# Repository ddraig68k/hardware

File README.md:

# CAD files for Y Ddraig

This repository contains the Schematics and any other relevant files for a [Motorola 68000 computer](https://ddraig68k.com) in KiCAD format. The files for the main computer boards as well as any of the expansion boards are present in the repository.

The libraries used in the project are contained in the ddraig-libs folder inside the repo, to use them in KiCAD, go to Configure Paths and add a custom path DDRAIGLIB which points to the ddraig-libs folder.

## Y Ddraig

Welsh for *The Dragon*, Y Ddraig is my [Motorola 68000](https://en.wikipedia.org/wiki/Motorola_68000) computer. 

| **Specifications** |
|-|
|68000 CPU running at 10Mhz.|
|512K EEPROM |
|1M of Static RAM|
|8M Dynamic RAM|
|2 Serial ports|
|Parallel port|
|PS/2 keyboard and mouse|
|IDE interface|
|Real-time clock|
|4 Expansion slots|

<br />

# Design Files
[Y Ddraig 68000 PCB](yddraig)

**Expansion Cards**

* [Dual SID Audio card](expansion/AudioSID) - two MOS 6581/8580 SID chips for Commodore 64 style audio

* [YM2151 Audio card](expansion/AudioYM2151) - Yamaha FM synthesis chip as used in many arcade games

* [RTL8019 Ethernet card](expansion/Eth8019) - 10BASE-T Ethernet using the Realtek RTL8019AS

* [TMS9918 Graphics card](expansion/GfxTMS9918) - the video chip used in the Sega SG-1000, ColecoVision and MSX1

* [V9958 Graphics card](expansion/GfxV9958) - Yamaha's successor to the TMS9918, as used in the MSX2+

* [V9990 Graphics card](expansion/GfxV9990) - Yamaha's follow up to the V9958 with higher resolutions

* [VGA Graphics card](expansion/GfxVGA) - FPGA based VGA video generation

* [Sega Megadrive joypad card](expansion/JoypadController) - reads standard 3 or 6-button Sega Megadrive/Genesis controllers

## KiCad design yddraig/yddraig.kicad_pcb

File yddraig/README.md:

## Y Ddraig hardware

### CPU, RAM and ROM

The CPU used by Y Ddraig is the [Motorola 68000](https://en.wikipedia.org/wiki/Motorola_68000) running at 10 MHz. The 68000 has a 16-bit data bus and 24-bit address bus internally runs as a full 32-bit machine. The 68000 has 8 general purpose data registers *D0-D7* and 8 address registers *A0-A7*. The address register A7 is also used as a special purpose register holding the *stack pointer*.

There is 512K of EEPROM available supplied by two 256K x 8-bit SST39SF020 devices for the ODD and EVEN addresses.

RAM is provided by two 512K x 8-bit AS6C4008 Static RAM devices giving a total of 1024K of available memory. There is also the option of adding an additional Dynamic RAM to expand the memory up to a total of 9MB.

### Memory Mapping

As the 68000 is a memory mapped device the address decoding is handled by a Xilinx XC95C108 CPLD. In addition to the address decoding the CPLD is also used as the DRAM controller.

The memory map is as follows:

| Device | Start Address | End Address |
|-|-|-|
| Static Ram | 0x000000 | 0x0FFFFF |
| Dynamic RAM | 0x100000 | 0x900000 |
| Slot1 Data | 0xA00000 | 0xAFFFFF |
| Slot2 Data | 0xB00000 | 0xBFFFFF |
| Slot3 Data | 0xC00000 | 0xCFFFFF |
| Slot4 Data | 0xD00000 | 0xDFFFFF |
| DUART | 0xF7F000 | 0xF7F0FF |
| PIT | 0xF7F100 | 0xF7F1FF |
| KBD | 0xF7F200 | 0xF7F2FF |
| IDE | 0xF7F300 | 0xF7F3FF |
| RTC | 0xF7F400 | 0xF7F4FF |
| Slot1 | 0xF7F500 | 0xF7F5FF |
| Slot2 | 0xF7F600 | 0xF7F6FF |
| Slot3 | 0xF7F700 | 0xF7F7FF |
| Slot4 | 0xF7F800 | 0xF7F8FF |
| ROM | 0xF80000 | 0xFFFFFF |

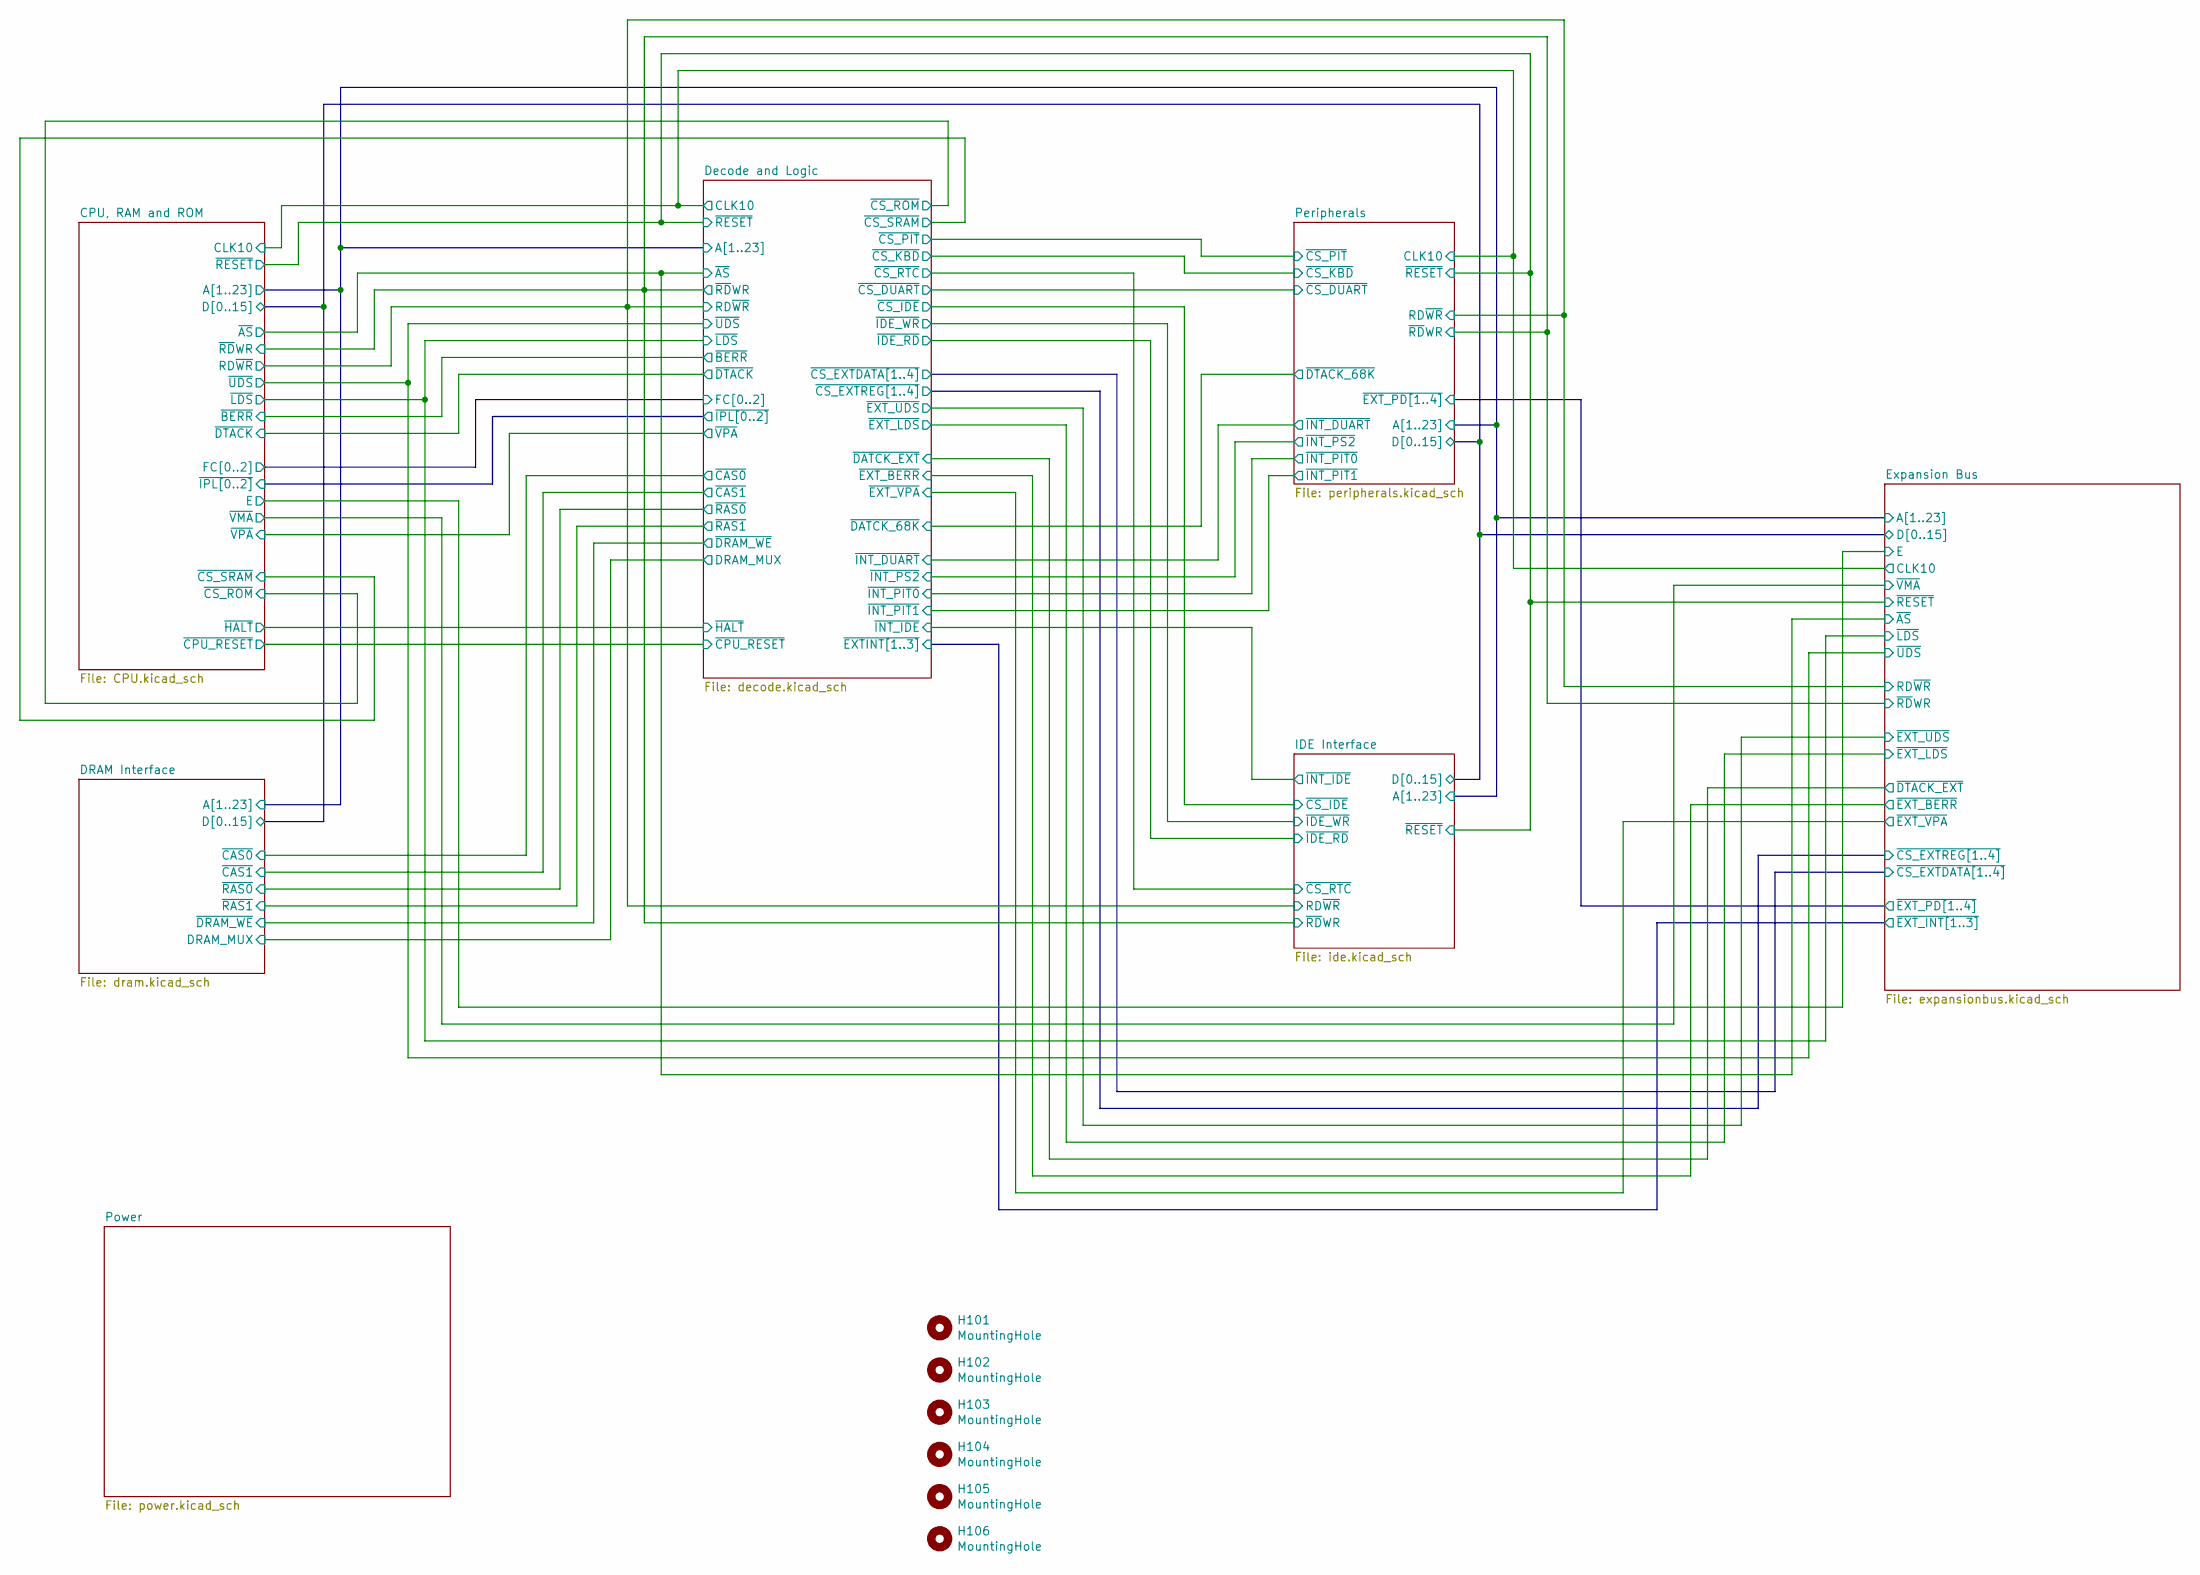
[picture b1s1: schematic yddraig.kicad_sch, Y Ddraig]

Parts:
H101, H102, H103, H104, H105, H106: MountingHole; MountingHole_4.3mm_M4

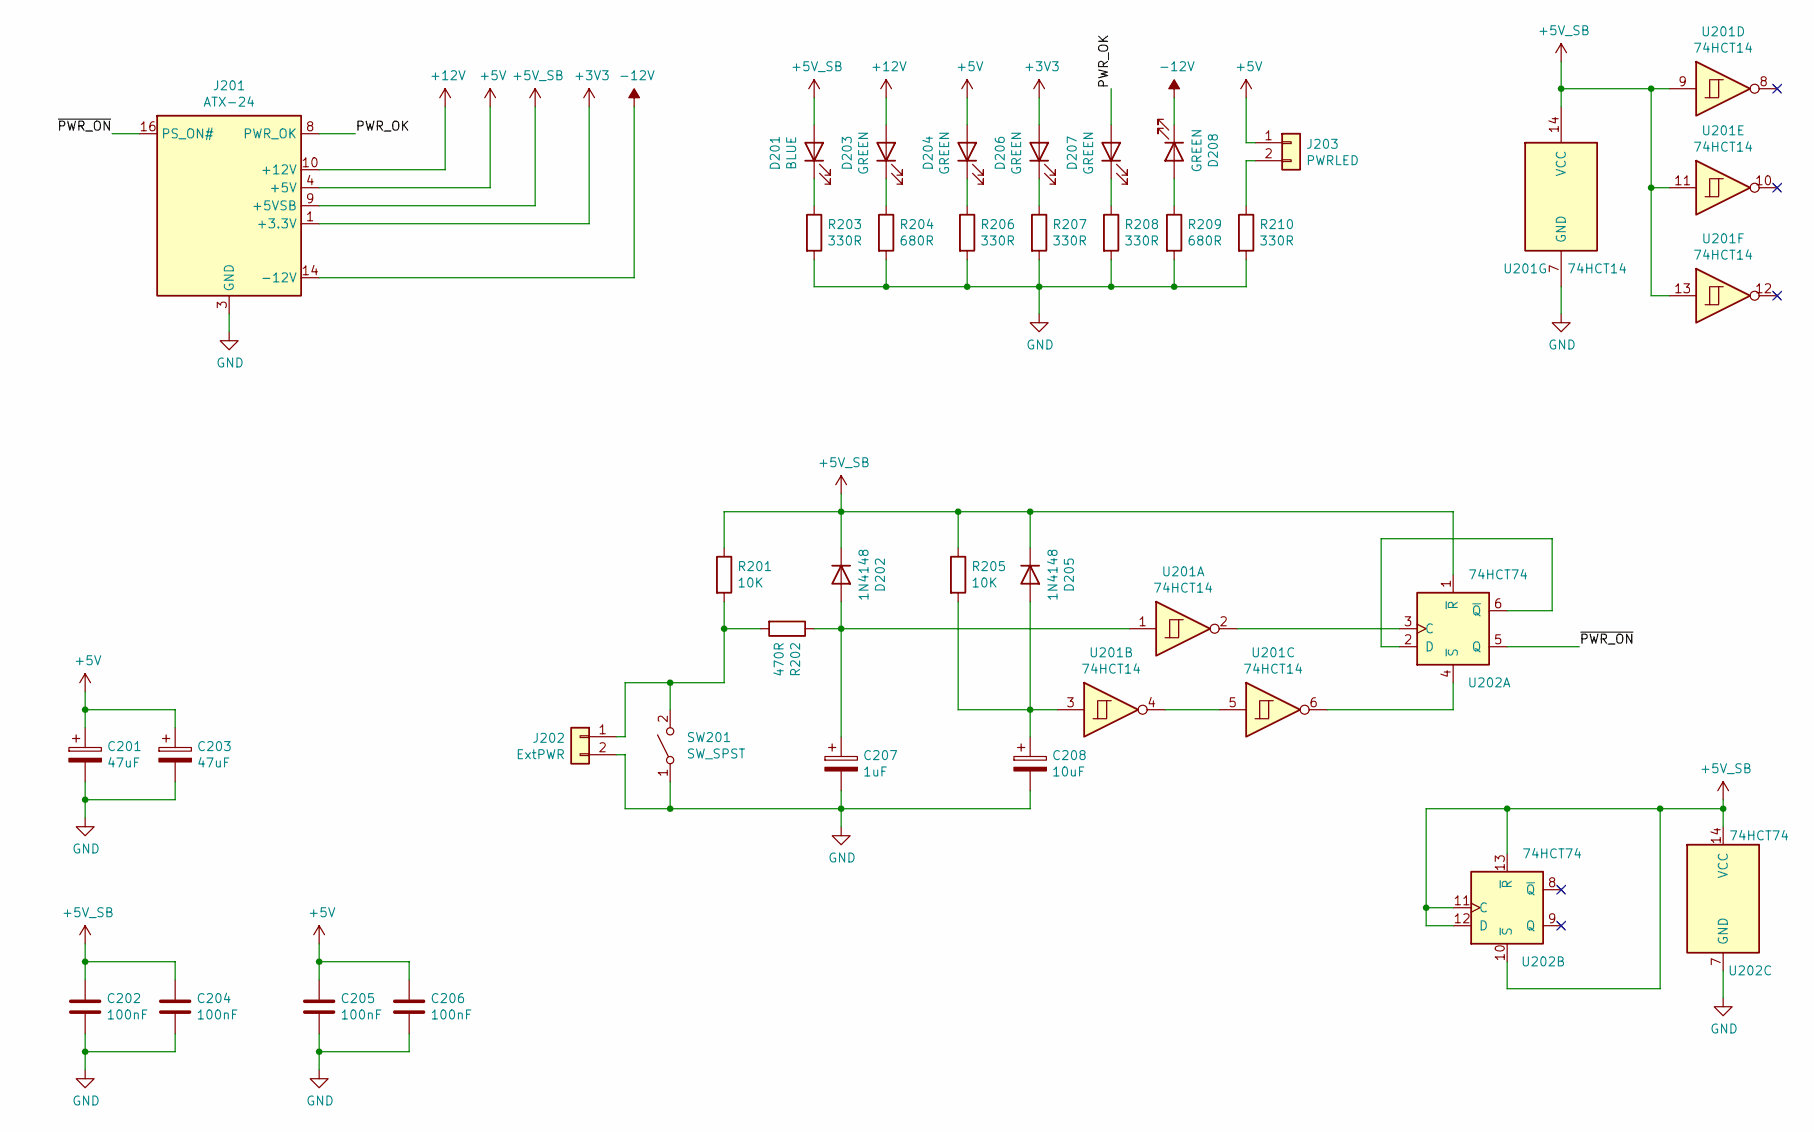
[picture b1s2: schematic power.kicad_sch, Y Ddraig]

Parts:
C201, C203: 47uF; CP_Radial_D5.0mm_P2.50mm
C202, C204, C205, C206: 100nF; C_Disc_D3.8mm_W2.6mm_P2.50mm
C207: 1uF; CP_Radial_D5.0mm_P2.50mm
C208: 10uF; CP_Radial_D5.0mm_P2.50mm
D201: BLUE; LED_D5.0mm
D202, D205: 1N4148; D_DO-35_SOD27_P7.62mm_Horizontal
D203, D204, D206, D207, D208: GREEN; LED_D5.0mm
J201: ATX-24; 1-1775099-3
J202: ExtPWR; PinHeader_1x02_P2.54mm_Vertical
J203: PWRLED; PinHeader_1x02_P2.54mm_Vertical
R201, R205: 10K; R_Axial_DIN0207_L6.3mm_D2.5mm_P10.16mm_Horizontal
R202: 470R; R_Axial_DIN0207_L6.3mm_D2.5mm_P10.16mm_Horizontal
R203, R206, R207, R208, R210: 330R; R_Axial_DIN0207_L6.3mm_D2.5mm_P10.16mm_Horizontal
R204, R209: 680R; R_Axial_DIN0207_L6.3mm_D2.5mm_P10.16mm_Horizontal
SW201: SW_SPST; SW_PUSH_6mm_H4.3mm
U201: 74HCT14; DIP-14_W7.62mm_Socket
U202: 74HCT74; DIP-14_W7.62mm_Socket

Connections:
+3V3: D206.2 (A), J201.1 (+3.3V), J201.2 (+3.3V), J201.12 (+3.3V), J201.13 (+3.3V); also elsewhere on the board
+5V: C201.1, C203.1, C205.1, C206.1, D204.2 (A), J201.4 (+5V), J201.6 (+5V), J201.21 (+5V), J201.22 (+5V), J201.23 (+5V), J203.1; also elsewhere on the board
+5V_SB: C202.1, C204.1, D201.2 (A), D202.1 (K), D205.1 (K), J201.9 (+5VSB), R201.1, R205.1, U201.9, U201.11, U201.13, U201.14 (VCC), U202.1 (~R), U202.10 (~S), U202.11 (C), U202.12 (D), U202.13 (~R), U202.14 (VCC); also elsewhere on the board
+12V: D203.2 (A), J201.10 (+12V), J201.11 (+12V); also elsewhere on the board
-12V: D208.1 (K), J201.14 (-12V); also elsewhere on the board
/Power/PWR_OK: D207.2 (A), J201.8 (PWR_OK)
/Power/~PWR_ON: J201.16 (PS_ON#), U202.5 (Q)
GND: C201.2, C202.2, C203.2, C204.2, C205.2, C206.2, C207.2, C208.2, J201.3 (GND), J201.5 (GND), J201.7 (GND), J201.15 (GND), J201.17 (GND), J201.18 (GND), J201.19 (GND), J201.24 (GND), J202.2, R203.2, R204.2, R206.2, R207.2, R208.2, R209.2, R210.2, SW201.1 (A), U201.7 (GND), U202.7 (GND); also elsewhere on the board
unnamed: D201.1 (K), R203.1
unnamed: C207.1, D202.2 (A), R202.1, U201.1
unnamed: D203.1 (K), R204.1
unnamed: D204.1 (K), R206.1
unnamed: C208.1, D205.2 (A), R205.2, U201.3
unnamed: D206.1 (K), R207.1
unnamed: D207.1 (K), R208.1
unnamed: D208.2 (A), R209.1
unnamed: J202.1, R201.2, R202.2, SW201.2 (B)
unnamed: J203.2, R210.1
unnamed: U201.4, U201.5
unnamed: U201.2, U202.3 (C)
unnamed: U202.2 (D), U202.6 (~Q)
unnamed: U201.6, U202.4 (~S)

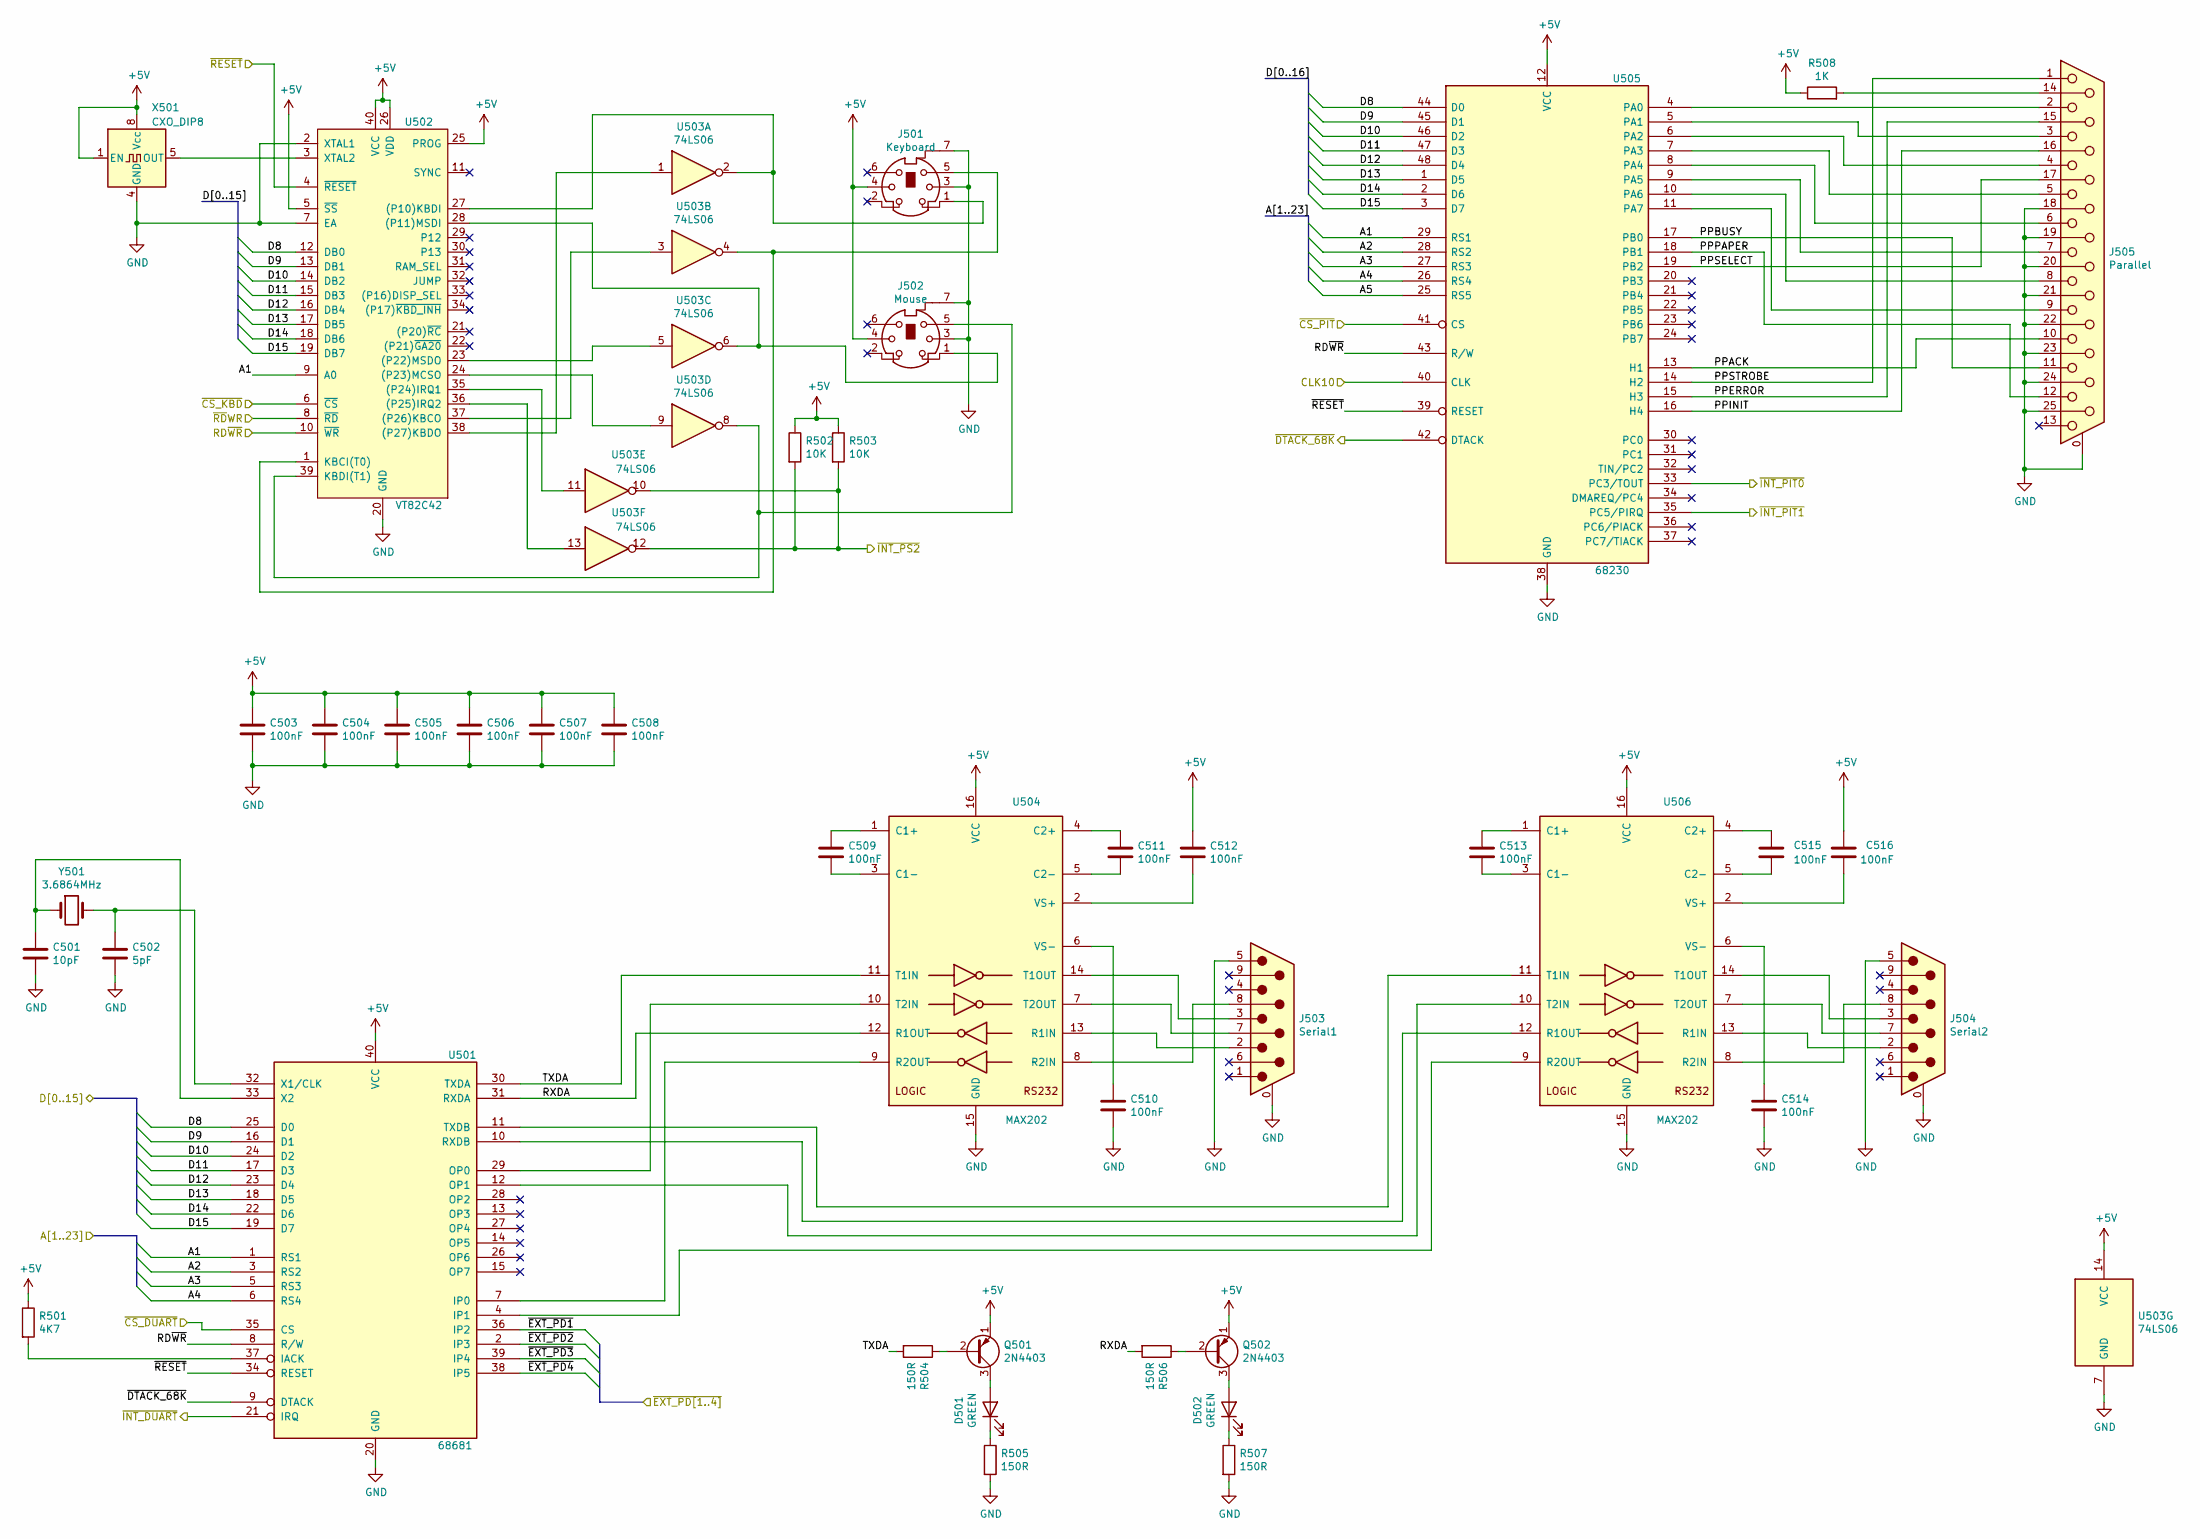
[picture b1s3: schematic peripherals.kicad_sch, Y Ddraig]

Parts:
C501: 10pF; C_Disc_D3.8mm_W2.6mm_P2.50mm
C502: 5pF; C_Disc_D3.8mm_W2.6mm_P2.50mm
C503, C504, C505, C506, C507, C508, C509, C510, C511, C512, C513, C514, C515, C516: 100nF; C_Disc_D3.8mm_W2.6mm_P2.50mm
D501, D502: GREEN; LED_D5.0mm
J501: Keyboard; MINI-DIN-6-FULL-SHIELD
J502: Mouse; MINI-DIN-6-FULL-SHIELD
J503: Serial1; DSUB-9_Male_Horizontal_P2.77x2.84mm_EdgePinOffset4.94mm_Hou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
J504: Serial2; DSUB-9_Male_Horizontal_P2.77x2.84mm_EdgePinOffset4.94mm_Hou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
J505: Parallel; DSUB-25_Female_Horizontal_P2.77x2.84mm_EdgePinOffset7.70mm_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
Q501, Q502: 2N4403; TO-92
R501: 4K7; R_Axial_DIN0207_L6.3mm_D2.5mm_P10.16mm_Horizontal
R502, R503: 10K; R_Axial_DIN0207_L6.3mm_D2.5mm_P10.16mm_Horizontal
R504, R505, R506, R507: 150R; R_Axial_DIN0207_L6.3mm_D2.5mm_P10.16mm_Horizontal
R508: 1K; R_Axial_DIN0207_L6.3mm_D2.5mm_P10.16mm_Horizontal
U501: 68681; DIP-40_W15.24mm_Socket
U502: VT82C42; DIP-40_W15.24mm_Socket
U503: 74LS06; DIP-14_W7.62mm_Socket
U504, U506: MAX202; DIP-16_W7.62mm_Socket
U505: 68230; DIP-48_W15.24mm_Socket
X501: CXO_DIP8; Oscillator_DIP-8
Y501: 3.6864MHz; Crystal_HC18-U_Vertical

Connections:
+5V: C503.1, C504.1, C505.1, C506.1, C507.1, C508.1, C512.1, C516.2, J501.4, J502.4, Q501.1 (E), Q502.1 (E), R501.1, R502.1, R503.1, R508.1, U501.40 (VCC), U502.5 (~SS), U502.25 (PROG), U502.26 (VDD), U502.40 (VCC), U503.14 (VCC), U504.16 (VCC), U505.12 (VCC), U506.16 (VCC), X501.1 (EN), X501.8 (Vcc); also elsewhere on the board
/CPU, RAM and ROM/A1: U501.1 (RS1), U502.9 (A0), U505.29 (RS1); also elsewhere on the board
/CPU, RAM and ROM/A2: U501.3 (RS2), U505.28 (RS2); also elsewhere on the board
/CPU, RAM and ROM/A3: U501.5 (RS3), U505.27 (RS3); also elsewhere on the board
/CPU, RAM and ROM/A4: U501.6 (RS4), U505.26 (RS4); also elsewhere on the board
/CPU, RAM and ROM/A5: U505.25 (RS5); also elsewhere on the board
/CPU, RAM and ROM/CLK10: U505.40 (CLK); also elsewhere on the board
/CPU, RAM and ROM/RD~WR: U501.8 (R/W), U502.10 (~WR), U505.43 (R/W); also elsewhere on the board
/CPU, RAM and ROM/~RDWR: U502.8 (~RD); also elsewhere on the board
/Decode and Logic/~CS_DUART: U501.35 (CS); also elsewhere on the board
/Decode and Logic/~CS_KBD: U502.6 (~CS); also elsewhere on the board
/Decode and Logic/~CS_PIT: U505.41 (CS); also elsewhere on the board
/Decode and Logic/~INT_DUART: U501.21 (IRQ); also elsewhere on the board
/Decode and Logic/~INT_PIT0: U505.33 (PC3/TOUT); also elsewhere on the board
/Decode and Logic/~INT_PIT1: U505.35 (PC5/PIRQ); also elsewhere on the board
/Decode and Logic/~INT_PS2: R502.2, R503.2, U503.10, U503.12; also elsewhere on the board
/Decode and Logic/~RESET: U501.34 (RESET), U502.4 (~RESET), U505.39 (RESET); also elsewhere on the board
/Expansion Bus/~EXT_PD1: U501.36 (IP2); also elsewhere on the board
/Expansion Bus/~EXT_PD2: U501.2 (IP3); also elsewhere on the board
/Expansion Bus/~EXT_PD3: U501.39 (IP4); also elsewhere on the board
/Expansion Bus/~EXT_PD4: U501.38 (IP5); also elsewhere on the board
/Peripherals/D8: U501.25 (D0), U502.12 (DB0), U505.44 (D0); also elsewhere on the board
/Peripherals/D9: U501.16 (D1), U502.13 (DB1), U505.45 (D1); also elsewhere on the board
/Peripherals/D10: U501.24 (D2), U502.14 (DB2), U505.46 (D2); also elsewhere on the board
/Peripherals/D11: U501.17 (D3), U502.15 (DB3), U505.47 (D3); also elsewhere on the board
/Peripherals/D12: U501.23 (D4), U502.16 (DB4), U505.48 (D4); also elsewhere on the board
/Peripherals/D13: U501.18 (D5), U502.17 (DB5), U505.1 (D5); also elsewhere on the board
/Peripherals/D14: U501.22 (D6), U502.18 (DB6), U505.2 (D6); also elsewhere on the board
/Peripherals/D15: U501.19 (D7), U502.19 (DB7), U505.3 (D7); also elsewhere on the board
/Peripherals/PPACK: J505.10, U505.13 (H1)
/Peripherals/PPBUSY: J505.11, U505.17 (PB0)
/Peripherals/PPERROR: J505.15, U505.15 (H3)
/Peripherals/PPINIT: J505.16, U505.16 (H4)
/Peripherals/PPPAPER: J505.12, U505.18 (PB1)
/Peripherals/PPSELECT: J505.17, U505.19 (PB2)
/Peripherals/PPSTROBE: J505.1, U505.14 (H2)
/Peripherals/RXDA: R506.2, U501.31 (RXDA), U504.12 (R1OUT)
/Peripherals/TXDA: R504.2, U501.30 (TXDA), U504.11 (T1IN)
/Peripherals/~DTACK_68K: U501.9 (DTACK), U505.42 (DTACK); also elsewhere on the board
GND: C501.2, C502.2, C503.2, C504.2, C505.2, C506.2, C507.2, C508.2, C510.2, C514.2, J501.3, J501.7, J502.3, J502.7, J503.0 (PAD), J503.5, J504.0 (PAD), J504.5, J505.0 (PAD), J505.18, J505.19, J505.20, J505.21, J505.22, J505.23, J505.24, J505.25, R505.2, R507.2, U501.20 (GND), U502.2 (XTAL1), U502.7 (EA), U502.20 (GND), U503.7 (GND), U504.15 (GND), U505.38 (GND), U506.15 (GND), X501.4 (GND); also elsewhere on the board
unnamed: D501.2 (A), Q501.3 (C)
unnamed: D501.1 (K), R505.1
unnamed: D502.2 (A), Q502.3 (C)
unnamed: D502.1 (K), R507.1
unnamed: J505.14, R508.2
unnamed: Q501.2 (B), R504.1
unnamed: Q502.2 (B), R506.1
unnamed: R501.2, U501.37 (IACK)
unnamed: U501.7 (IP0), U504.9 (R2OUT)
unnamed: U501.4 (IP1), U506.9 (R2OUT)
unnamed: U501.29 (OP0), U504.10 (T2IN)
unnamed: U501.12 (OP1), U506.10 (T2IN)
unnamed: U501.10 (RXDB), U506.12 (R1OUT)
unnamed: U501.11 (TXDB), U506.11 (T1IN)
unnamed: C502.1, U501.32 (X1/CLK), Y501.2
unnamed: C501.1, U501.33 (X2), Y501.1
unnamed: U502.35 (IRQ1), U503.11
unnamed: U502.36 (IRQ2), U503.13
unnamed: J501.5, U502.1 (KBCI), U503.4
unnamed: U502.37 (KBCO), U503.3
unnamed: J502.5, U502.39 (KBDI), U503.8
unnamed: U502.38 (KBDO), U503.1
unnamed: J501.1, U502.27 (P10/KBDI), U503.2
unnamed: J502.1, U502.28 (P11/MSDI), U503.6
unnamed: U502.23 (P22/MSDO), U503.5
unnamed: U502.24 (P23/MCSO), U503.9
unnamed: U502.3 (XTAL2), X501.5 (OUT)
unnamed: C509.1, U504.1 (C1+)
unnamed: C509.2, U504.3 (C1-)
unnamed: C511.1, U504.4 (C2+)
unnamed: C511.2, U504.5 (C2-)
unnamed: J503.2, U504.13 (R1IN)
unnamed: J503.8, U504.8 (R2IN)
unnamed: J503.3, U504.14 (T1OUT)
unnamed: J503.7, U504.7 (T2OUT)
unnamed: C512.2, U504.2 (VS+)
unnamed: C510.1, U504.6 (VS-)
unnamed: J505.2, U505.4 (PA0)
unnamed: J505.3, U505.5 (PA1)
unnamed: J505.4, U505.6 (PA2)
unnamed: J505.5, U505.7 (PA3)
unnamed: J505.6, U505.8 (PA4)
unnamed: J505.7, U505.9 (PA5)
unnamed: J505.8, U505.10 (PA6)
unnamed: J505.9, U505.11 (PA7)
unnamed: C513.1, U506.1 (C1+)
unnamed: C513.2, U506.3 (C1-)
unnamed: C515.1, U506.4 (C2+)
unnamed: C515.2, U506.5 (C2-)
unnamed: J504.2, U506.13 (R1IN)
unnamed: J504.8, U506.8 (R2IN)
unnamed: J504.3, U506.14 (T1OUT)
unnamed: J504.7, U506.7 (T2OUT)
unnamed: C516.1, U506.2 (VS+)
unnamed: C514.1, U506.6 (VS-)

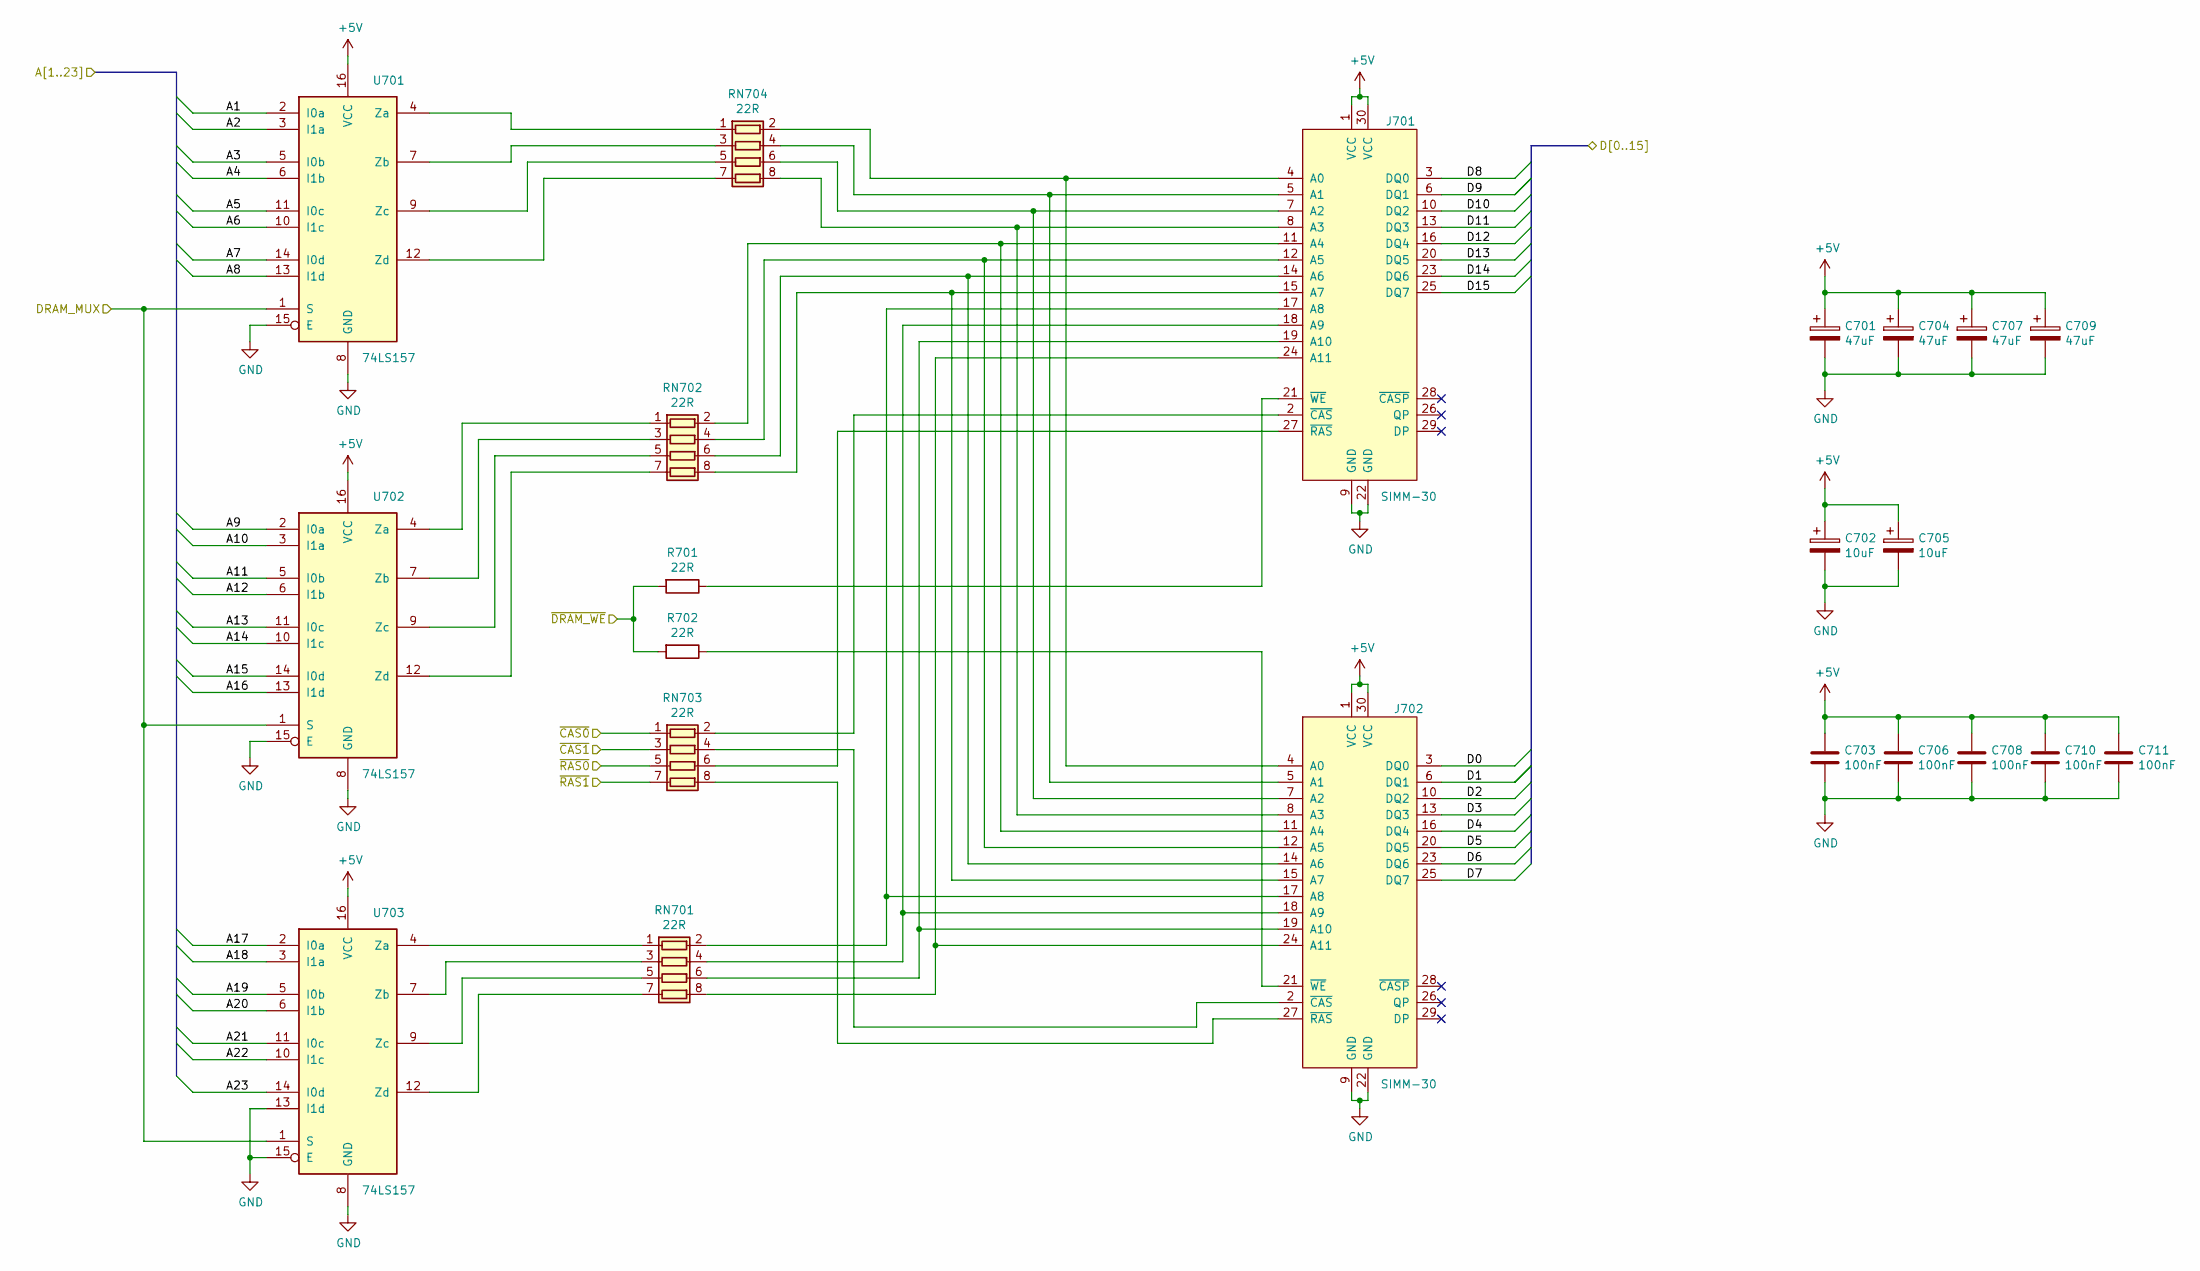
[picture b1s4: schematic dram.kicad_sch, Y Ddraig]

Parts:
C701, C704, C707, C709: 47uF; CP_Radial_D5.0mm_P2.50mm
C702, C705: 10uF; CP_Radial_D5.0mm_P2.50mm
C703, C706, C708, C710, C711: 100nF; C_Disc_D3.8mm_W2.6mm_P2.50mm
J701, J702: SIMM-30
R701, R702: 22R; R_Axial_DIN0207_L6.3mm_D2.5mm_P10.16mm_Horizontal
RN701, RN702, RN703, RN704: 22R; R_Array_SIP8
U701, U702, U703: 74LS157; DIP-16_W7.62mm_Socket

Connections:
+5V: C701.1, C702.1, C703.1, C704.1, C705.1, C706.1, C707.1, C708.1, C709.1, C710.1, C711.1, J701.1 (VCC), J701.30 (VCC), J702.1 (VCC), J702.30 (VCC), U701.16 (VCC), U702.16 (VCC), U703.16 (VCC); also elsewhere on the board
/CPU, RAM and ROM/A1: U701.2 (I0a); also elsewhere on the board
/CPU, RAM and ROM/A2: U701.3 (I1a); also elsewhere on the board
/CPU, RAM and ROM/A3: U701.5 (I0b); also elsewhere on the board
/CPU, RAM and ROM/A4: U701.6 (I1b); also elsewhere on the board
/CPU, RAM and ROM/A5: U701.11 (I0c); also elsewhere on the board
/CPU, RAM and ROM/A6: U701.10 (I1c); also elsewhere on the board
/CPU, RAM and ROM/A7: U701.14 (I0d); also elsewhere on the board
/CPU, RAM and ROM/A8: U701.13 (I1d); also elsewhere on the board
/CPU, RAM and ROM/A9: U702.2 (I0a); also elsewhere on the board
/CPU, RAM and ROM/A10: U702.3 (I1a); also elsewhere on the board
/CPU, RAM and ROM/A11: U702.5 (I0b); also elsewhere on the board
/CPU, RAM and ROM/A12: U702.6 (I1b); also elsewhere on the board
/CPU, RAM and ROM/A13: U702.11 (I0c); also elsewhere on the board
/CPU, RAM and ROM/A14: U702.10 (I1c); also elsewhere on the board
/CPU, RAM and ROM/A15: U702.14 (I0d); also elsewhere on the board
/CPU, RAM and ROM/A16: U702.13 (I1d); also elsewhere on the board
/CPU, RAM and ROM/A17: U703.2 (I0a); also elsewhere on the board
/CPU, RAM and ROM/A18: U703.3 (I1a); also elsewhere on the board
/CPU, RAM and ROM/A19: U703.5 (I0b); also elsewhere on the board
/CPU, RAM and ROM/A20: U703.6 (I1b); also elsewhere on the board
/CPU, RAM and ROM/A21: U703.11 (I0c); also elsewhere on the board
/CPU, RAM and ROM/A22: U703.10 (I1c); also elsewhere on the board
/CPU, RAM and ROM/A23: U703.14 (I0d); also elsewhere on the board
/DRAM Interface/DRAM_MUX: U701.1 (S), U702.1 (S), U703.1 (S); also elsewhere on the board
/DRAM Interface/~CAS0: RN703.1 (R1.1); also elsewhere on the board
/DRAM Interface/~CAS1: RN703.3 (R2.1); also elsewhere on the board
/DRAM Interface/~DRAM_WE: R701.2, R702.2; also elsewhere on the board
/DRAM Interface/~RAS0: RN703.5 (R3.1); also elsewhere on the board
/DRAM Interface/~RAS1: RN703.7 (R4.1); also elsewhere on the board
/Peripherals/D0: J702.3 (DQ0); also elsewhere on the board
/Peripherals/D1: J702.6 (DQ1); also elsewhere on the board
/Peripherals/D2: J702.10 (DQ2); also elsewhere on the board
/Peripherals/D3: J702.13 (DQ3); also elsewhere on the board
/Peripherals/D4: J702.16 (DQ4); also elsewhere on the board
/Peripherals/D5: J702.20 (DQ5); also elsewhere on the board
/Peripherals/D6: J702.23 (DQ6); also elsewhere on the board
/Peripherals/D7: J702.25 (DQ7); also elsewhere on the board
/Peripherals/D8: J701.3 (DQ0); also elsewhere on the board
/Peripherals/D9: J701.6 (DQ1); also elsewhere on the board
/Peripherals/D10: J701.10 (DQ2); also elsewhere on the board
/Peripherals/D11: J701.13 (DQ3); also elsewhere on the board
/Peripherals/D12: J701.16 (DQ4); also elsewhere on the board
/Peripherals/D13: J701.20 (DQ5); also elsewhere on the board
/Peripherals/D14: J701.23 (DQ6); also elsewhere on the board
/Peripherals/D15: J701.25 (DQ7); also elsewhere on the board
GND: C701.2, C702.2, C703.2, C704.2, C705.2, C706.2, C707.2, C708.2, C709.2, C710.2, C711.2, J701.9 (GND), J701.22 (GND), J702.9 (GND), J702.22 (GND), U701.8 (GND), U701.15 (E), U702.8 (GND), U702.15 (E), U703.8 (GND), U703.13 (I1d), U703.15 (E); also elsewhere on the board
unnamed: J701.4 (A0), J702.4 (A0), RN704.2 (R1.2)
unnamed: J701.5 (A1), J702.5 (A1), RN704.4 (R2.2)
unnamed: J701.7 (A2), J702.7 (A2), RN704.6 (R3.2)
unnamed: J701.8 (A3), J702.8 (A3), RN704.8 (R4.2)
unnamed: J701.11 (A4), J702.11 (A4), RN702.2 (R1.2)
unnamed: J701.12 (A5), J702.12 (A5), RN702.4 (R2.2)
unnamed: J701.14 (A6), J702.14 (A6), RN702.6 (R3.2)
unnamed: J701.15 (A7), J702.15 (A7), RN702.8 (R4.2)
unnamed: J701.17 (A8), J702.17 (A8), RN701.2 (R1.2)
unnamed: J701.18 (A9), J702.18 (A9), RN701.4 (R2.2)
unnamed: J701.19 (A10), J702.19 (A10), RN701.6 (R3.2)
unnamed: J701.24 (A11), J702.24 (A11), RN701.8 (R4.2)
unnamed: J701.2 (~CAS), RN703.2 (R1.2)
unnamed: J701.27 (~RAS), RN703.6 (R3.2)
unnamed: J701.21 (~WE), R701.1
unnamed: J702.2 (~CAS), RN703.4 (R2.2)
unnamed: J702.27 (~RAS), RN703.8 (R4.2)
unnamed: J702.21 (~WE), R702.1
unnamed: RN701.1 (R1.1), U703.4 (Za)
unnamed: RN701.3 (R2.1), U703.7 (Zb)
unnamed: RN701.5 (R3.1), U703.9 (Zc)
unnamed: RN701.7 (R4.1), U703.12 (Zd)
unnamed: RN702.1 (R1.1), U702.4 (Za)
unnamed: RN702.3 (R2.1), U702.7 (Zb)
unnamed: RN702.5 (R3.1), U702.9 (Zc)
unnamed: RN702.7 (R4.1), U702.12 (Zd)
unnamed: RN704.1 (R1.1), U701.4 (Za)
unnamed: RN704.3 (R2.1), U701.7 (Zb)
unnamed: RN704.5 (R3.1), U701.9 (Zc)
unnamed: RN704.7 (R4.1), U701.12 (Zd)

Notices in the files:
expansion/AudioSID/AudioSID.kicad_pcb:
© 2023 Stephen Moody
expansion/AudioYM2151/AudioYM2151.kicad_pcb:
© 2021 Stephen Moody
yddraig/yddraig.kicad_pcb:
© 2021 Stephen Moody - https://ddraig68k.com
